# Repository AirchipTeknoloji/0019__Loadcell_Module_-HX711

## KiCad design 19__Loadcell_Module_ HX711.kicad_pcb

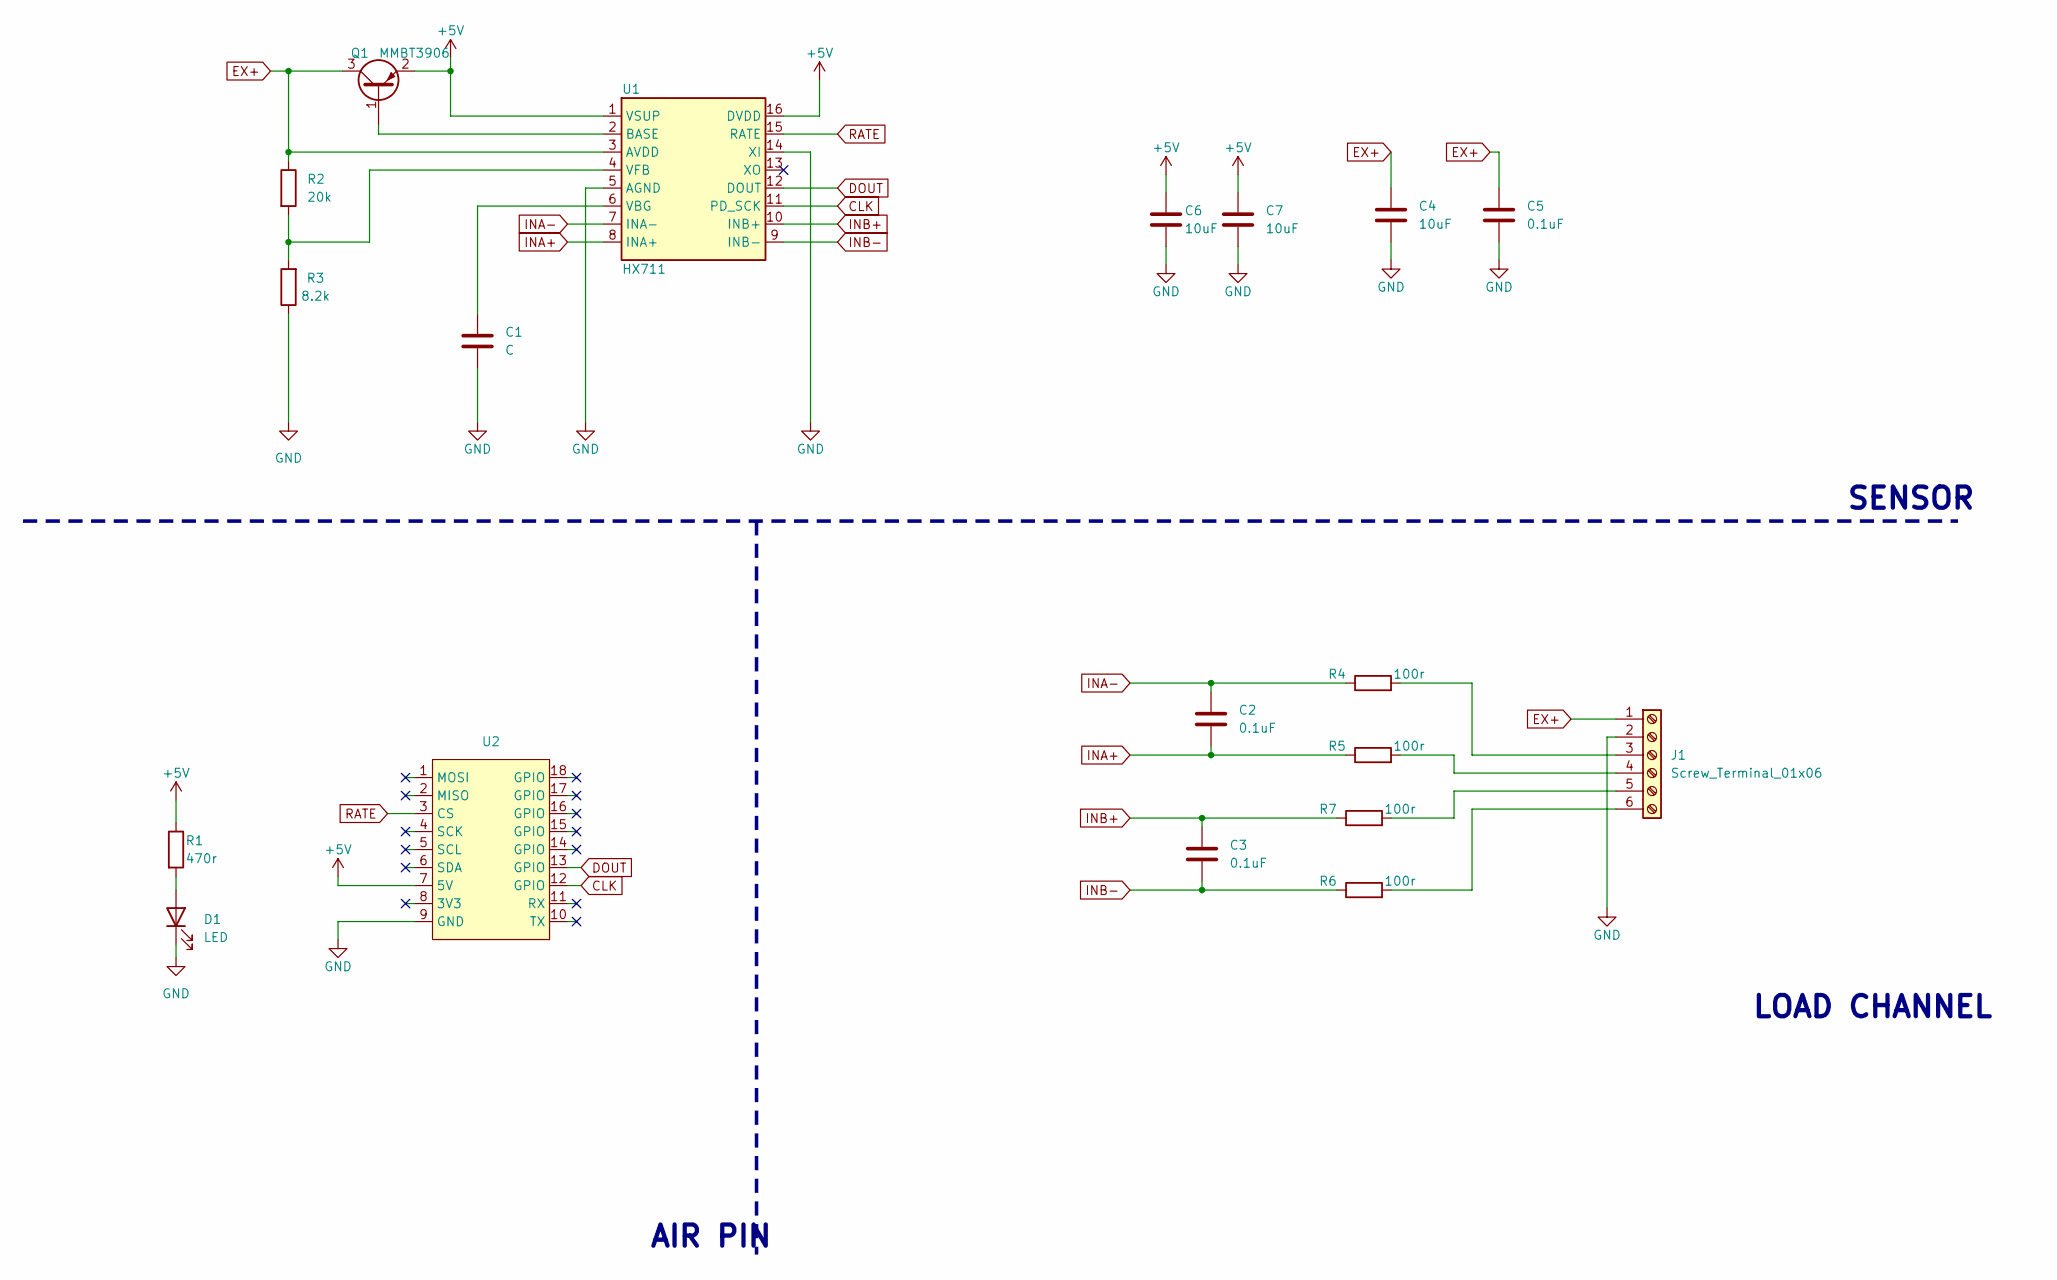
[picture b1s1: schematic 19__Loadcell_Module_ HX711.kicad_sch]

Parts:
C1: C; C_0805_2012Metric
C2, C3, C5: 0.1uF; C_0805_2012Metric
C4, C6, C7: 10uF; C_0805_2012Metric
D1: LED; LED_0805_2012Metric
J1: Screw_Terminal_01x06; TerminalBlock_Phoenix_PT-1,5-6-3.5-H_1x06_P3.50mm_Horizontal
Q1: MMBT3906; SOT-23
R1: 470r; R_0805_2012Metric
R2: 20k; R_0805_2012Metric
R3: 8.2k; R_0805_2012Metric
R4, R5, R6, R7: 100r; R_0805_2012Metric
U1: HX711; SOP-16_3.9x9.9mm_P1.27mm
U2: air_module

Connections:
+5V: C6.1, C7.1, Q1.2 (E), R1.1, U1.1 (VSUP), U1.16 (DVDD), U2.7 (5V)
CLK: U1.11 (PD_SCK), U2.12 (GPIO)
DOUT: U1.12 (DOUT), U2.13 (GPIO)
EX+: C4.1, C5.1, J1.1, Q1.3 (C), R2.1, U1.3 (AVDD)
GND: C1.2, C4.2, C5.2, C6.2, C7.2, D1.1 (K), J1.2, R3.1, U1.5 (AGND), U1.14 (XI), U2.9 (GND)
INA+: C2.2, R5.1, U1.8 (INA+)
INA-: C2.1, R4.1, U1.7 (INA-)
INB+: C3.1, R7.1, U1.10 (INB+)
INB-: C3.2, R6.1, U1.9 (INB-)
unnamed: D1.2 (A), R1.2
unnamed: J1.3, R4.2
unnamed: J1.4, R5.2
unnamed: J1.5, R7.2
unnamed: J1.6, R6.2
unnamed: Q1.1 (B), U1.2 (BASE)
unnamed: C1.1, U1.6 (VBG)
unnamed: R2.2, R3.2, U1.4 (VFB)
RATE: U1.15 (RATE), U2.3 (CS)

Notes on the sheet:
AIR PIN
LOAD CHANNEL
SENSOR

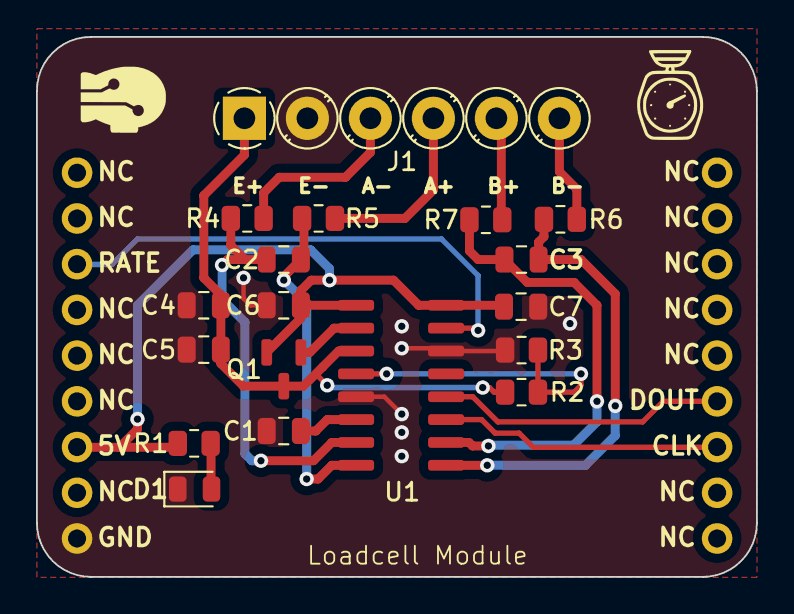
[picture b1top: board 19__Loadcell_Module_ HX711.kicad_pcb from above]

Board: 2 copper layers, 40.0 x 30.0 mm, 19 parts (0 on the bottom side), 18 nets.
